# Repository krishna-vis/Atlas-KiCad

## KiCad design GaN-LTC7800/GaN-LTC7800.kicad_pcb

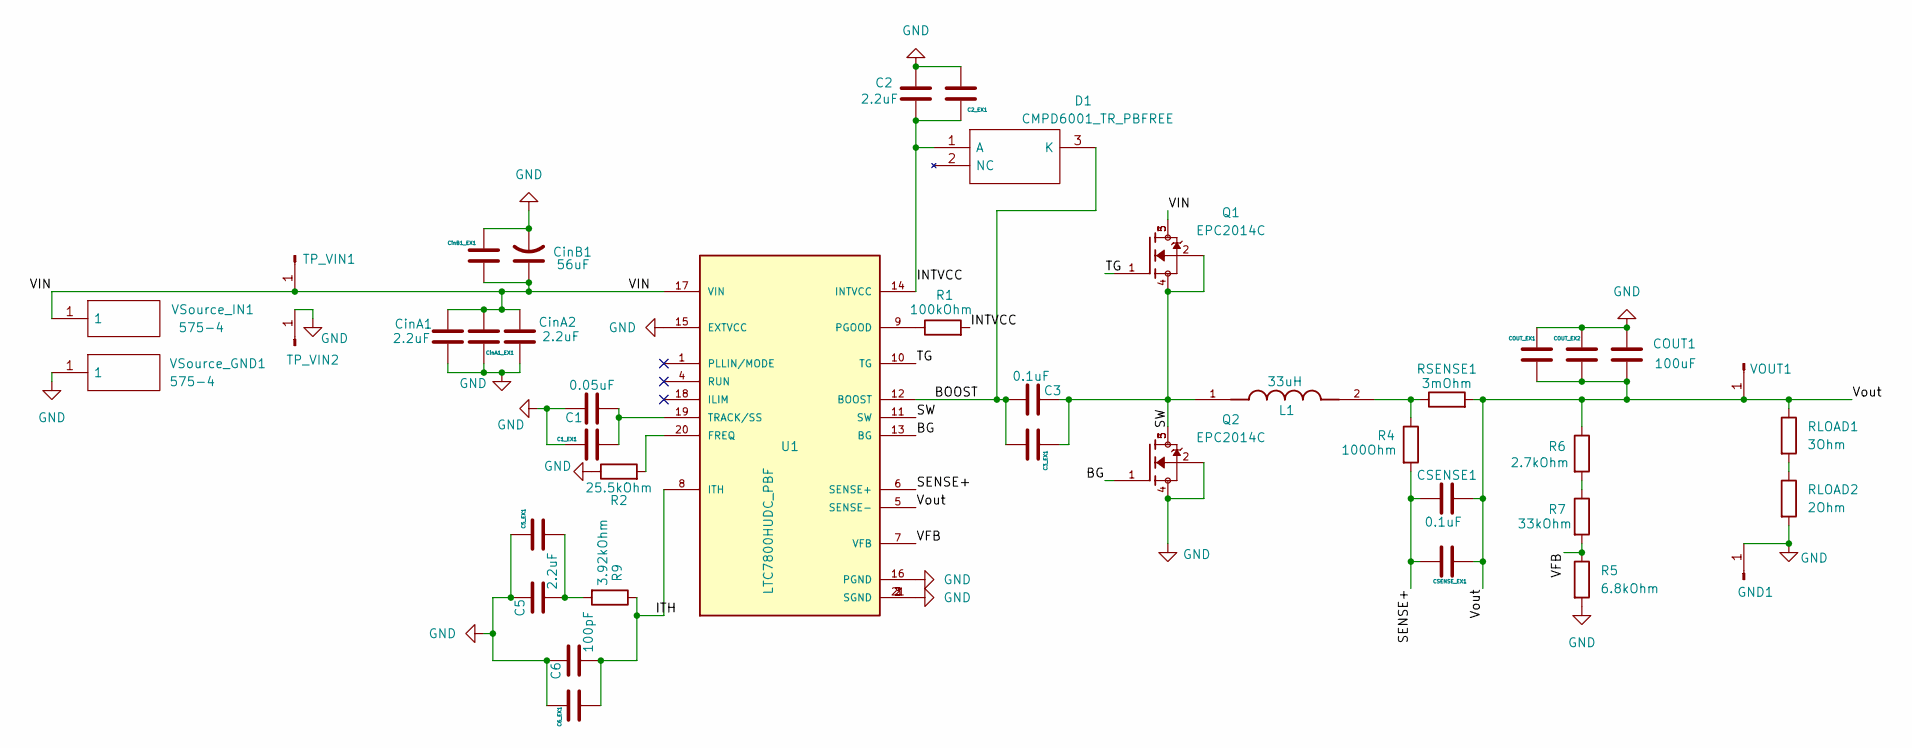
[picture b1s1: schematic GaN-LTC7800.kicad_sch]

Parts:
C1: 0.05uF; C_0805_2012Metric; LCSC C49678
C1_EX1, C2_EX1, C3_EX1, C5_EX1, C6_EX1: C_0805_2012Metric_Pad1.18x1.45mm_HandSolder
C2, C5: 2.2uF; C_0805_2012Metric; LCSC C19110
C3: 0.1uF; C_0805_2012Metric; LCSC C49678
C6: 100pF; C_0805_2012Metric; LCSC C1970
COUT1: 100uF; C_0805_2012Metric; LCSC C141660
COUT_EX1, COUT_EX2: C_0805_2012Metric_Pad1.18x1.45mm_HandSolder
CSENSE1: 0.1uF; C_0805_2012Metric; LCSC C49678
CSENSE_EX1: C_0805_2012Metric_Pad1.18x1.45mm_HandSolder
CinA1, CinA2: 2.2uF; C_0805_2012Metric; LCSC C19110
CinA1_EX1: C_0805_2012Metric_Pad1.18x1.45mm_HandSolder
CinB1: 56uF; CP_EIA-7343-31_Kemet-D; LCSC C465937
CinB1_EX1: C_0805_2012Metric_Pad1.18x1.45mm_HandSolder
D1: CMPD6001_TR_PBFREE; SOT95P230X109-3N; Manufacturer_Part_Number CMPD6001 TR PBFREE; Mouser Part Number 610-CMPD6001
GND1: PinHeader_1x01_P2.54mm_Vertical
L1: 33uH; IND_XGL1010-333MED; PARTREV 08/24/22
Q1, Q2: EPC2014C; TRANS_EPC2014C; PARTREV N/A
R1: 100kOhm; R_0201_0603Metric; LCSC C14675
R2: 25.5kOhm; R_0201_0603Metric; LCSC C861257
R4: 100Ohm; R_0201_0603Metric; LCSC C105588
R5: 6.8kOhm; R_0201_0603Metric; LCSC C2907055
R6: 2.7kOhm; R_0201_0603Metric; LCSC C2907008
R7: 33kOhm; R_0201_0603Metric; LCSC C2907028
R9: 3.92kOhm; R_0201_0603Metric; LCSC C4168160
RLOAD1: 3Ohm; R_0201_0603Metric; LCSC C23157
RLOAD2: 2Ohm; R_0201_0603Metric; LCSC C22977
RSENSE1: 3mOhm; R_0201_0603Metric; LCSC C7256520
TP_VIN1, TP_VIN2: PinHeader_1x01_P2.54mm_Vertical
U1: LTC7800HUDC_PBF; QFN50P400X300X80-21N; LCSC C690192
VOUT1: PinHeader_1x01_P2.54mm_Vertical
VSource_GND1: 575-4; 5754; Manufacturer_Part_Number 575-4; Mouser Part Number 534-575-4
VSource_IN1: 575-4; 5754; Manufacturer_Part_Number 575-4; Mouser Part Number 534-575-4

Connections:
/BG: Q2.1, U1.13 (BG)
/BOOST: C3.1, C3_EX1.2, D1.3 (K), U1.12 (BOOST)
/INTVCC: C2.2, C2_EX1.1, D1.1 (A), R1.2, U1.14 (INTVCC)
/ITH: C6.2, C6_EX1.2, R9.1, U1.8 (ITH)
/SENSE+: CSENSE1.1, CSENSE_EX1.2, R4.2, U1.6 (SENSE+)
/SW: C3.2, C3_EX1.1, L1.1, Q1.2, Q1.4, Q2.3, Q2.5, U1.11 (SW)
/TG: Q1.1, U1.10 (TG)
/VFB: R5.1, R7.2, U1.7 (VFB)
/VIN: CinA1.1, CinA1_EX1.2, CinA2.1, CinB1.1, CinB1_EX1.1, Q1.3, Q1.5, TP_VIN1.1, U1.17 (VIN), VSource_IN1.1
/Vout: COUT1.1, COUT_EX1.2, COUT_EX2.2, CSENSE1.2, CSENSE_EX1.1, R6.1, RLOAD1.1, RSENSE1.2, U1.5 (SENSE-), VOUT1.1
GND: C1.1, C1_EX1.1, C2.1, C2_EX1.2, C5.1, C5_EX1.1, C6.1, C6_EX1.1, COUT1.2, COUT_EX1.1, COUT_EX2.1, CinA1.2, CinA1_EX1.1, CinA2.2, CinB1.2, CinB1_EX1.2, GND1.1, Q2.2, Q2.4, R2.1, R5.2, RLOAD2.2, TP_VIN2.1, U1.2 (SGND), U1.3 (SGND), U1.15 (EXTVCC), U1.16 (PGND), U1.21 (SGND), VSource_GND1.1
unnamed: C5.2, C5_EX1.2, R9.2
unnamed: L1.2, R4.1, RSENSE1.1
unnamed: R6.2, R7.1
unnamed: RLOAD1.2, RLOAD2.1
unnamed: R2.2, U1.20 (FREQ)
unnamed: R1.1, U1.9 (PGOOD)
unnamed: C1.2, C1_EX1.2, U1.19 (TRACK/SS)

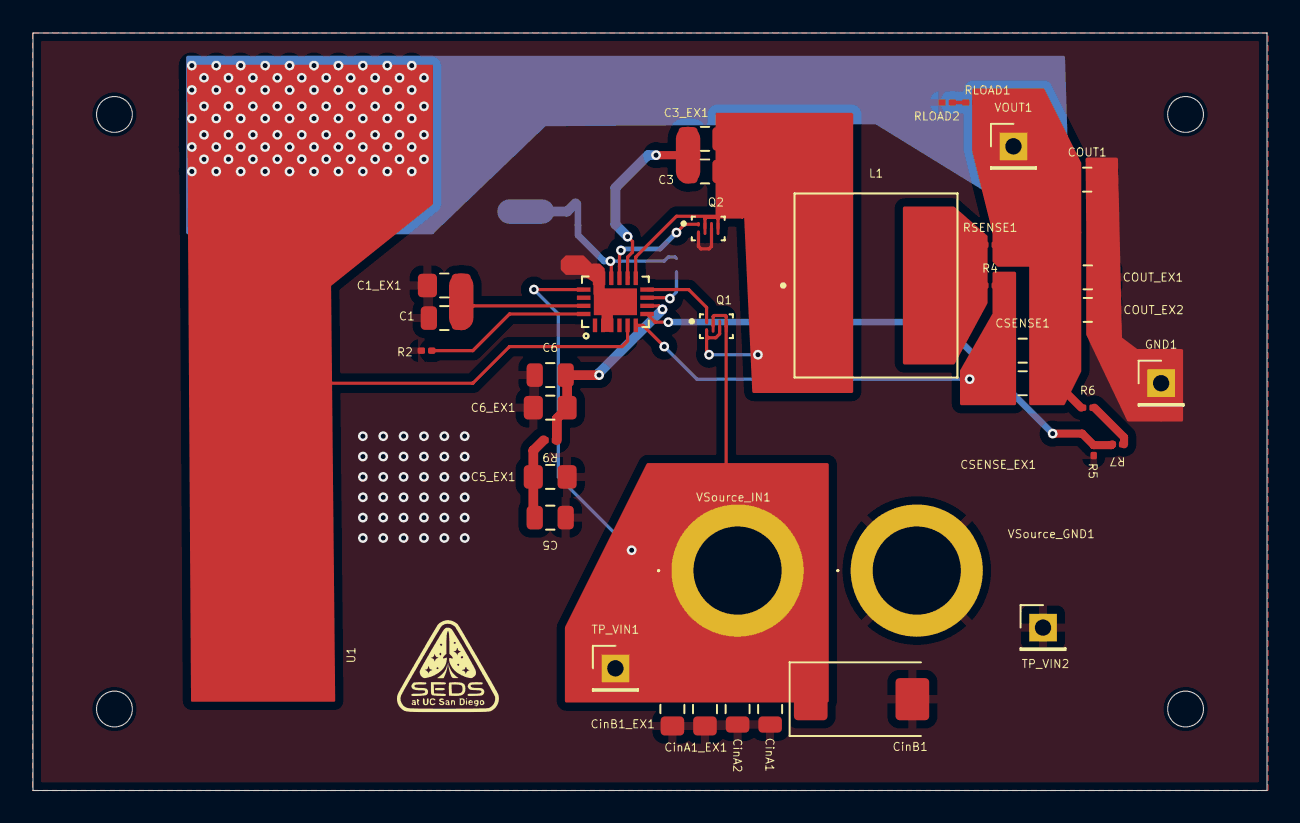
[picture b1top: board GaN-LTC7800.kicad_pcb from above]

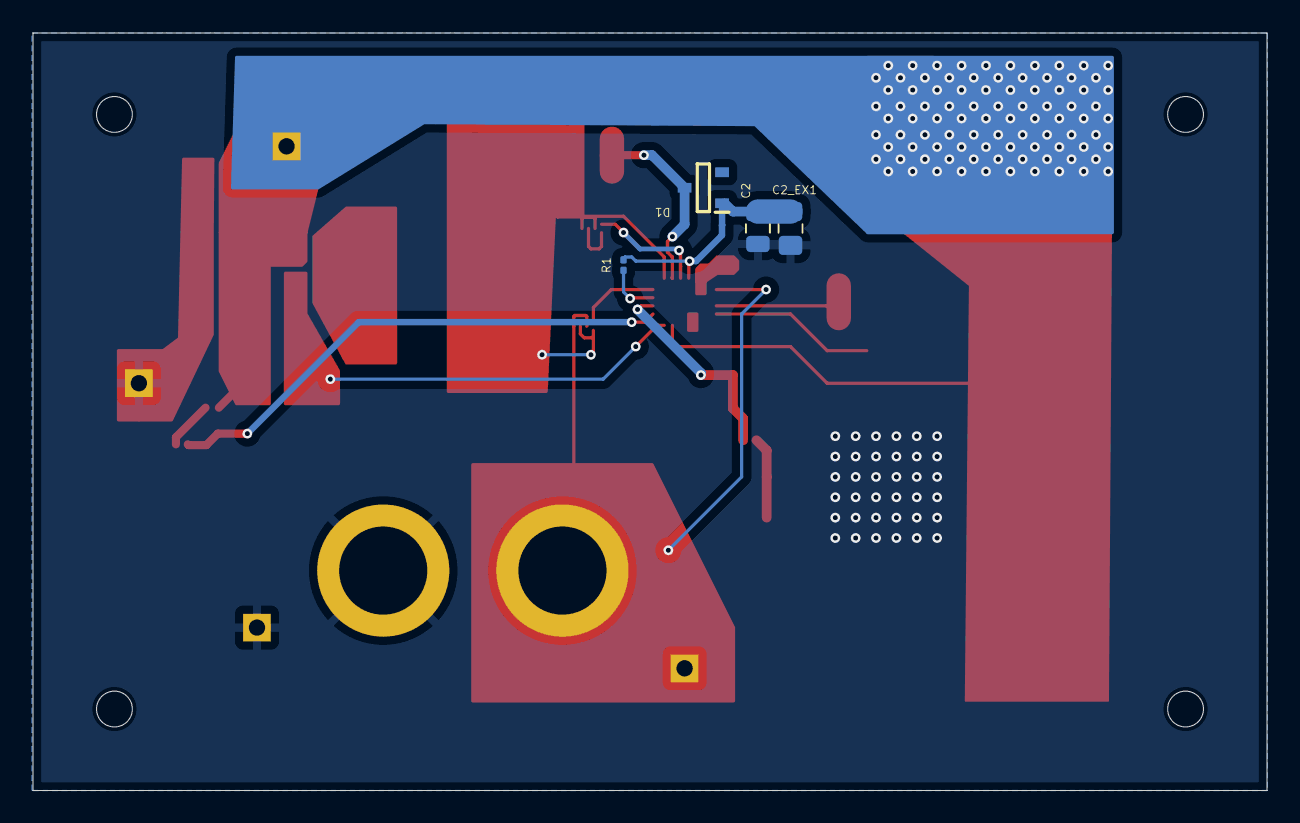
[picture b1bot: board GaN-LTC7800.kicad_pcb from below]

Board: 2 copper layers, 75.8 x 46.5 mm, 41 parts (4 on the bottom side), 18 nets.

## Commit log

2025-10-19 Initial commit of KiCad project
2025-10-20 Began wiring the PCB for the GaN circuit
2025-10-25 Finished GaN schematic
2025-10-25 Assigned values to parts, replaced inductor with CoilCraft one
2025-10-27 Renamed GaN Circuit to GaN LTC7891 Controller Circuit
2025-10-27 Renamed projects and added files for new controller circuits
2025-10-29 Schematics for Si and GaN for LTC7800 controller
2025-11-01 Updated footprints for LTC7800
2025-11-01 Updated shematics
2025-11-02 Si Schematic Update
2025-11-02 Updated MOSFET
2025-11-02 FET fixes
2025-11-08 fixing flip issue
2025-11-08 Started GaN PCB
2025-11-08 Finished draft of GaN PCB
2025-11-08 Updated GaN schematic
2025-11-08 Changed test points to header pins
2025-11-08 power traces sortof done
2025-11-08 Changed font size and names on PCB
2025-11-09 connections and such
2025-11-09 GaN PCB update
2025-11-15 new GaN switches, added alt projects
2025-11-16 GaN simple layout done
2025-11-16 alternates
2025-11-16 alternates good
2026-01-10 logos
2026-01-11 Updating PCBs for preassembly
2026-01-11 Updated for preassembly
2026-01-11 mounting holes
2026-01-12 minor edits
